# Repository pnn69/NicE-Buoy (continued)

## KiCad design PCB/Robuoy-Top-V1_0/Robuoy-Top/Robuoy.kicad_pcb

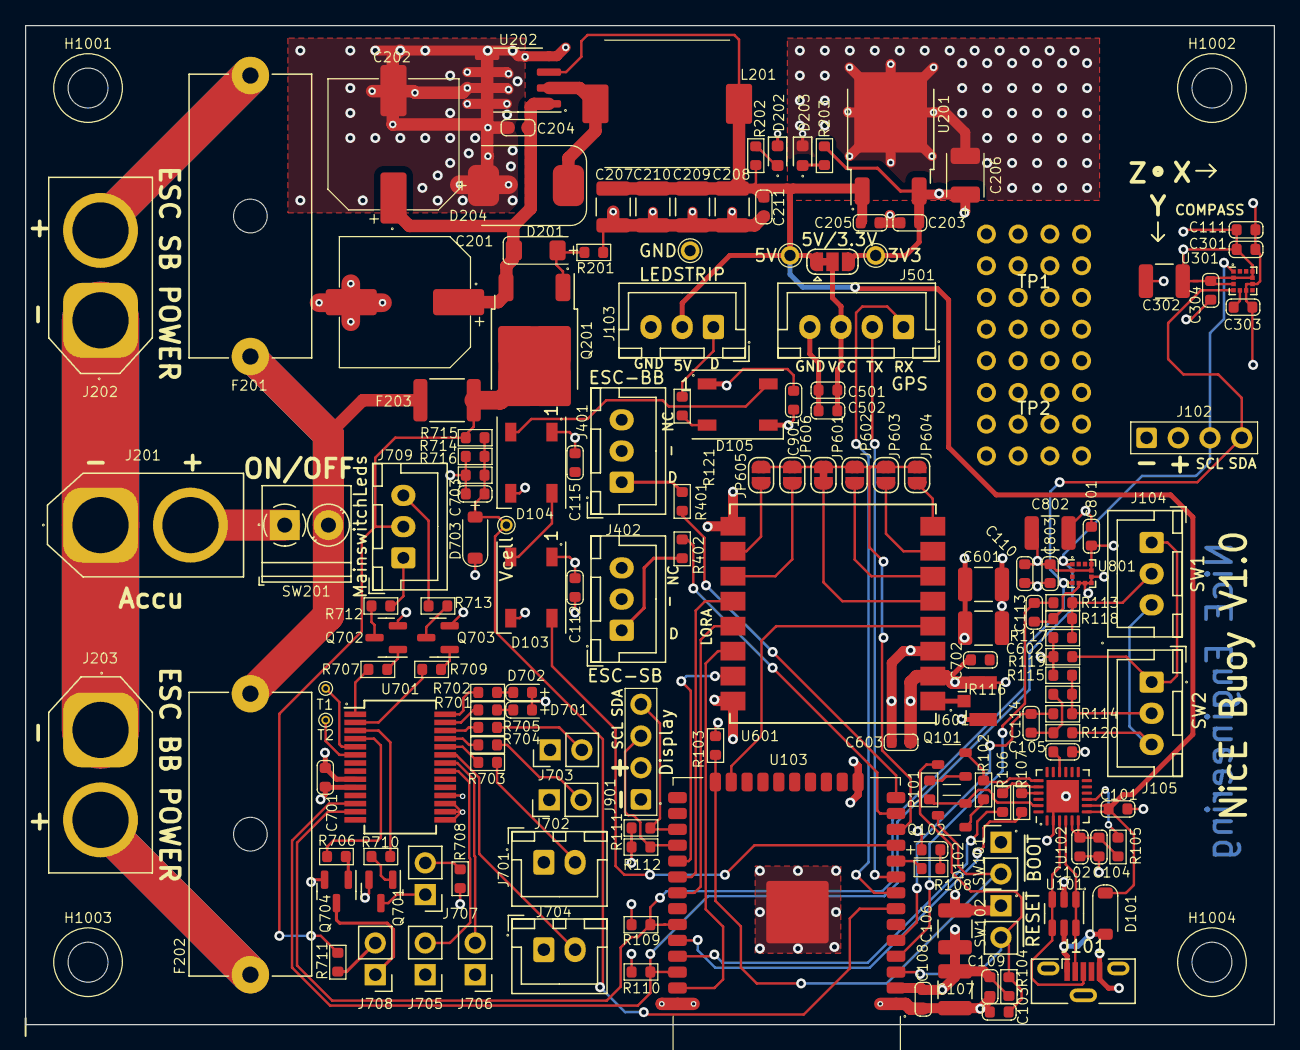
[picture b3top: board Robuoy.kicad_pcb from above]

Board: 4 copper layers, 100.0 x 80.0 mm, 160 parts (0 on the bottom side), 99 nets.

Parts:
C101, C102, C105: 4.7u; C_0603
C103, C104, C108, C109, C110, C111, C112, C115, C203, C204, C205, C211, C301, C303, C304, C501, C502, C603, C701, C702, C801, C803, C901: 100n; C_0603
C106, C107, C207, C208, C209, C210, C601, C602: 100u/16V; C_1210_3225Metric
C113, C114, C703: 1n; C_0603
C201, C202: 220u/50V; CP_ALU_D10x10.5
C206: 100u/6.3V; CP_TANT_3.5x2.8x1.9
C302, C802: 10u; C_1210_3225Metric
D101, D703: SM4007PL; D_SOD-123_2.85x1.8x1.3
D102, D701: GREEN; LED_0603
D103, D104, D105: WS2812B; LED_WS2812B_PLCC4_5.0x5.0mm_P3.2mm
D201: ZMM5V6-M; D_MiniMELF
D202: 5V; LED_0603_1608Metric
D203: 3.3V; LED_0603_1608Metric
D204: SS36-E3/57T; D_SMC_7.1x6.2x2.65
D702: RED; LED_0603
F201, F202: 10A/T; Fuseholder_Cylinder-5x20mm_Schurter_0031_8201_Horizontal_Op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
F203: 3AT; Fuse_1812_4532Metric
H1001, H1002, H1003, H1004: MountingHole; NPTH_M3
J101: 1051330011; USB_Micro-B_Molex-105133-0001
J102, J901: Display; Header_1x04_P2.54_Male
J103: LEDSTRIP; JST_XH_B3B-XH-A_1x03_P2.50mm_Vertical
J104: SW1; JST_XH_B3B-XH-A_1x03_P2.50mm_Vertical
J105: SW2; JST_XH_B3B-XH-A_1x03_P2.50mm_Vertical
J201: Accu; AMASS_XT60-M_1x02_P7.20mm_Vertical
J202: ESC SB POWER; AMASS_XT60-F_1x02_P7.20mm_Vertical
J203: ESC BB POWER; AMASS_XT60-F_1x02_P7.20mm_Vertical
J401: ESC-BB; JST_XH_B3B-XH-A_1x03_P2.50mm_Vertical
J402: ESC-SB; JST_XH_B3B-XH-A_1x03_P2.50mm_Vertical
J501: GPS; JST_XH_B4B-XH-A_1x04_P2.50mm_Vertical
J601: Conn_Coaxial; U.FL_Hirose_U.FL-R-SMT-1_Vertical
J701: LED1; JST_XH_B2B-XH-A_1x02_P2.50mm_Vertical
J702: LED2; PinHeader_1x02_P2.54mm_Vertical
J703: LED3; PinHeader_1x02_P2.54mm_Vertical
J704: SW1; JST_XH_B2B-XH-A_1x02_P2.50mm_Vertical
J705: SW3; PinHeader_1x02_P2.54mm_Vertical
J706: SW2; PinHeader_1x02_P2.54mm_Vertical
J707: 3.3V switch; PinHeader_1x02_P2.54mm_Vertical
J708: Vbatt switch; PinHeader_1x02_P2.54mm_Vertical
J709: MainswitchLeds; JST_XH_B3B-XH-A_1x03_P2.50mm_Vertical
JP501: 5V/3.3V; SolderJumper-3_P1.3mm_Bridged12_RoundedPad1.0x1.5mm
JP601: D0; SolderJumper-2_P1.3mm_Bridged_RoundedPad1.0x1.5mm
JP602: D1; SolderJumper-2_P1.3mm_Open_RoundedPad1.0x1.5mm
JP603: D2; SolderJumper-2_P1.3mm_Open_RoundedPad1.0x1.5mm
JP604: D3; SolderJumper-2_P1.3mm_Open_RoundedPad1.0x1.5mm
JP605: D4; SolderJumper-2_P1.3mm_Open_RoundedPad1.0x1.5mm
JP606: D5; SolderJumper-2_P1.3mm_Open_RoundedPad1.0x1.5mm
L201: 68uH/3A; L_11.5x10.0mm
Q101, Q102: 2N7002; SOT-23_1.4x3_P0.95
Q201: NCE01P30K; TO-252-2
Q701, Q702, Q703, Q704: MMBT5551L; SOT-23
R101, R102, R103, R104, R105, R115, R116, R117, R118: 10K; R_0603
R106, R107: 120E; R_0603
R108, R203, R701, R702, R706, R707, R709, R710, R714, R716: 1k; R_0603
R109, R110, R111, R112: 2.2k; R_0603
R113, R114, R119, R120, R121, R201, R401, R402, R703, R704, R705, R708, R711: 100; R_0603
R202: 1.5k; R_0603
R712, R713: 4.7k; R_0603
R715: 6.2k; R_0603
SW101: ~{BOOT}; PinHeader_1x02_P2.54mm_Vertical
SW102: ~{RESET}; PinHeader_1x02_P2.54mm_Vertical
SW201: ON/OFF; TerminalBlock_Phoenix_PT-1,5-2-3.5-H_1x02_P3.50mm_Horizontal
TP1: RW1; ReworkPins
TP2: RW2; ReworkPins
TP201: GND; Testpoint_0.9x1.5
TP202: 3V3; Testpoint_0.9x1.5
TP203: 5V; Testpoint_0.9x1.5
TP701: Vcell; Testpoint_0.6x1.0
TP702: T1; Testpoint_0.4x0.7
TP703: T2; Testpoint_0.4x0.7
U101: SRV05-4; SOT-23-6
U102: CP2104-F03-GMR; QFN-24-1EP_4x4mm_P0.5mm_EP2.6x2.6mm
U103: ESP32-WROOM-32E_(visible_peripherals); ESP32-WROOM-32
U201: AP7363; TO-252-2
U202: XL1509-5.0E1; SOIC-8_3.9x4.9mm_P1.27mm
U301: LSM303C; LGA-12_2x2mm_P0.5mm
U601: Ai-Thinker-Ra-01; Ai-Thinker-Ra-01-LoRa
U701: MCP23017_SS; SSOP-28_5.3x10.2mm_P0.65mm
U801: LIS2HH12; LGA-12_2x2mm_P0.5mm

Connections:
+3.3V: C106.1, C107.1, C108.1, C109.1, C110.1, C111.1, C112.1, C115.1, C205.1, C206.1, C301.1, C302.1, C304.1, C601.1, C602.1, C603.1, C701.1, C702.1, C801.1, C802.1, C803.1, C901.1, D102.2 (A), D103.1 (VDD), D104.1 (VDD), D105.1 (VDD), D701.2 (A), D702.2 (A), D703.1 (K), J102.2, J901.2, JP501.3 (B), R103.1, R104.1, R109.1, R110.1, R111.1, R112.1, R115.2, R117.2, R119.2, R203.2, R708.1, TP202.1, U103.2 (VDD), U201.3 (VO), U301.2 (CS_XL), U301.3 (CS_MAG), U301.9 (VDD), U301.10 (VDDIO), U601.3 (VDD), U701.9 (VDD), U701.18 (~RESET), U801.2 (~CS), U801.9 (Vdd), U801.10 (Vdd_IO)
+5V: C101.2, C203.1, C207.1, C208.1, C209.1, C210.1, C211.1, D101.1 (K), J103.2, JP501.1 (A), L201.2, R202.1, TP203.1, U102.7 (REGIN), U102.8 (VBUS), U201.1 (VI), U202.3 (FB)
+28V: F203.2, J709.2, Q201.2 (D), R711.1, R715.1
/Accumonitor/GREEN: J709.1, R712.1
/Accumonitor/RED: J709.3, R713.2
/Accumonitor/Vbatt: C703.1, D703.2 (A), R714.1, R715.2, R716.1, TP701.1, U103.7 (GPIO35)
/CPU/ESC_BB: R401.1, U103.14 (MTDI/MISO/D2/GPIO12)
/CPU/ESC_SB: R402.1, U103.13 (MTMS/SCK/CLK/GPIO14)
/CPU/GPSRX: J501.1, U103.8 (GPIO32)
/CPU/GPSTX: J501.2, U103.9 (GPIO33)
/CPU/LEDS: D103.4 (DIN), U103.11 (GPIO26)
/CPU/RADIO_1: U103.37 (MOSI/GPIO23), U601.14 (MOSI)
/CPU/RADIO_2: U103.31 (MISO/GPIO19), U601.13 (MISO)
/CPU/RADIO_3: U103.30 (SCK/GPIO18), U601.12 (SCK)
/CPU/RADIO_4: U103.29 (CS/GPIO5), U601.15 (~NSS)
/CPU/RADIO_5: U103.23 (MTDO/CS/CMD/GPIO15), U601.4 (~RESET)
/CPU/RADIO_6: JP601.1 (A), JP602.1 (A), JP603.1 (A), JP604.1 (A), JP605.1 (A), JP606.1 (A), U103.12 (GPIO27)
/CPU/SCL: J102.3, R110.2, U103.36 (SCL/GPIO22), U301.1 (SCL/SPC), U701.12 (SCK), U801.1 (SCL/SPC)
/CPU/SCL_DISP: J901.3, R112.2, U103.28 (TXD/GPIO17)
/CPU/SDA: J102.4, R109.2, U103.33 (SDA/GPIO21), U301.4 (SDA/SDI/SDO), U701.13 (SDA), U801.4 (SDA/SDI)
/CPU/SDA_DISP: J901.4, R111.2, U103.27 (RXD/GPIO16)
/GPS/Vext: C501.1, C502.1, J501.3, JP501.2 (C)
/PSU/ACC: J201.2, SW201.1 (A)
/PSU/POWER: F201.2, F202.2, F203.1, SW201.2 (B)
DR0: Q102.3 (C), R103.2, SW101.2, U103.24 (D0/GPIO2)
DTR: Q102.2 (E), R101.2, U102.23 (DTR)
EN: C103.1, Q101.3 (C), R104.2, SW102.2, U103.3 (CHIP_PU/EN)
GND: C101.1, C102.1, C103.2, C104.1, C105.1, C106.2, C107.2, C108.2, C109.2, C110.2, C111.2, C112.2, C113.2, C114.2, C115.2, C201.2, C202.2, C203.2, C204.2, C205.2, C206.2, C207.2, C208.2, C209.2, C210.2, C211.2, C301.2, C302.2, C303.2, C304.2, C501.2, C502.2, C601.2, C602.2, C603.2, C701.2, C702.2, C703.2, C801.2, C802.2, C803.2, C901.2, D103.3 (VSS), D104.3 (VSS), D105.3 (VSS), D202.1 (K), D203.1 (K), D204.2 (A), J101.5 (GND), J102.1, J103.3, J201.1, J202.1, J203.1, J401.2, J402.2, J501.4, J601.2 (Ext), J701.1, J702.1, J703.1, J704.1, J705.1, J706.1, J901.1, Q701.2 (E), Q702.2 (E), Q703.2 (E), Q704.2 (E), R116.1, R118.1, R120.1, R201.1, R714.2, R716.2, SW101.1, SW102.1, TP201.1, U101.2 (VN), U102.2 (GND), U102.25 (GND), U103.1 (GND), U103.15 (GND), U103.38 (GND), U103.39 (GND), U201.2 (GND), U202.4 (~EN), U202.5 (GND), U202.6 (GND), U202.7 (GND), U202.8 (GND), U301.6 (GND), U301.8 (GND), U601.2 (GND), U601.9 (GND), U601.16 (GND), U701.10 (VSS), U701.15 (A0), U701.16 (A1), U701.17 (A2), U801.5 (RES), U801.6 (GND), U801.7 (GND), U801.8 (GND)
LED1: R703.1, U701.24 (GPA3)
LED2: R704.1, U701.25 (GPA4)
LED3: R705.1, U701.26 (GPA5)
unnamed: D101.2 (A), J101.1 (VBUS), U101.5 (VP)
unnamed: D102.1 (K), R108.2
unnamed: D103.2 (DOUT), D104.4 (DIN)
unnamed: D104.2 (DOUT), D105.4 (DIN)
unnamed: D105.2 (DOUT), R121.2
unnamed: D201.2 (A), Q201.1 (G), R201.2
unnamed: C201.1, C202.1, C204.1, D201.1 (K), Q201.3 (S), U202.1 (VIN)
unnamed: D202.2 (A), R202.2
unnamed: D203.2 (A), R203.1
unnamed: D204.1 (K), L201.1, U202.2 (OUT)
unnamed: D701.1 (K), R701.2
unnamed: D702.1 (K), R702.2
unnamed: J101.3 (D+), U101.3 (IO2), U101.4 (IO3), U102.3 (D+)
unnamed: J101.2 (D-), U101.1 (IO1), U101.6 (IO4), U102.4 (D-)
unnamed: J103.1, R121.1
unnamed: J104.1, J105.1, R119.1
unnamed: J104.2, R113.2, R117.1, R118.2
unnamed: J104.3, J105.3, R120.2
unnamed: J105.2, R114.2, R115.1, R116.2
unnamed: F201.1, J202.2
unnamed: F202.1, J203.2
unnamed: J401.1, R401.2
unnamed: J402.1, R402.2
unnamed: J601.1 (In), U601.1 (ANT)
unnamed: J701.2, R703.2
unnamed: J702.2, R704.2
unnamed: J703.2, R705.2
unnamed: J707.1, Q701.3 (C)
unnamed: J707.2, R708.2
unnamed: J708.1, Q704.3 (C)
unnamed: J708.2, R711.2
unnamed: JP601.2 (B), U601.5 (DIO0)
unnamed: JP602.2 (B), U601.6 (DIO1)
unnamed: JP603.2 (B), U601.7 (DIO2)
unnamed: JP604.2 (B), U601.8 (DIO3)
unnamed: JP605.2 (B), U601.10 (DIO4)
unnamed: JP606.2 (B), U601.11 (DIO5)
unnamed: Q101.1 (B), R101.1
unnamed: Q102.1 (B), R102.1
unnamed: Q701.1 (B), R706.2
unnamed: Q702.1 (B), R707.2
unnamed: Q702.3 (C), R712.2
unnamed: Q703.1 (B), R709.2
unnamed: Q703.3 (C), R713.1
unnamed: Q704.1 (B), R710.2
unnamed: R106.2, U102.20 (RXD)
unnamed: R107.2, U102.21 (TXD)
unnamed: C102.2, C104.2, R105.1, U102.5 (VIO), U102.6 (VDD)
unnamed: C105.2, U102.16 (VPP)
unnamed: R105.2, U102.9 (~RSTb)
unnamed: R108.1, U103.10 (GPIO25)
unnamed: C113.1, R113.1, U103.4 (GPIO36)
unnamed: C114.1, R114.1, U103.5 (GPIO39)
unnamed: C303.1, U301.5 (C1)
unnamed: R701.1, U701.27 (GPA6)
unnamed: R702.1, U701.28 (GPA7)
unnamed: R707.1, U701.1 (GPB0)
unnamed: R709.1, U701.2 (GPB1)
unnamed: R706.1, U701.3 (GPB2)
unnamed: R710.1, U701.4 (GPB3)
unnamed: TP702.1, U701.5 (GPB4)
unnamed: TP703.1, U701.6 (GPB5)
RTS: Q101.2 (E), R102.2, U102.19 (RTS)
RX: R107.1, U103.34 (RXD/GPIO3)
SW1: J704.2, U701.23 (GPA2)
SW2: J706.2, U701.22 (GPA1)
SW3: J705.2, U701.21 (GPA0)
TX: R106.1, U103.35 (TXD/GPIO1)
